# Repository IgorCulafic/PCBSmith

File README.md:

# PCBSmith

PCBSmith is an open-source tool for designing printed circuit boards. The long-term goal is to describe a circuit in plain language and get a checked schematic, board layout and manufacturing files. Today it combines a schematic editor prototype with KiCad-based workflows for automatic routing, design review and laser-fabricated boards.

It is under active development. The current tools support supervised engineering work: component choices, design decisions and physical testing still need a person.

[Board gallery](docs/showcase/README.md) · [Concept to board](docs/showcase/development-process.md) · [Get started](#get-started) · [Design workflow](docs/production-usage.md) · [Development](docs/development.md)

## Boards made with PCBSmith

These are retained images from actual design projects. Captions distinguish CAD results, work in progress and physical fabrication.

<table>
<tr>
<td width="50%" align="center">
<br>
<strong>Thermometer</strong><br>
63 components, 53 routed nets and a custom outline. Accepted CAD proof; the render uses some proxy models.
</td>
<td width="50%" align="center">
<br>
<strong>Eight-channel protocol analyzer</strong><br>
A more complex controller and input-interface study. Placement prototype; routing and review remain open.
</td>
</tr>
<tr>
<td width="50%" align="center">
<br>
<strong>Pear Worm</strong><br>
LED rings following a pear outline, with custom silkscreen. Historical design prototype.
</td>
<td width="50%" align="center">
<br>
<strong>Lucky Clover</strong><br>
A compact LED board with a four-lobed outline. Historical design prototype.
</td>
</tr>
<tr>
<td width="50%" align="center">
<br>
<strong>DuoFilter</strong><br>
Two-sided RC filter: automatic routing, a resistor revision and a checked CAD handover.
</td>
<td width="50%" align="center">
<br>
<strong>TraceLimits — recent laser test</strong><br>
0.15–1.00 mm traces, a six-net corner test and two isolation widths. CAD handover complete; process measurements pending.
</td>
</tr>
</table>

The [full gallery](docs/showcase/README.md) includes routing views, laser-artwork comparisons and a two-sided plated-hole test coupon.

### From CAD to copper

<p align="center">

</p>

An early single-sided laser test, photographed by the builder. The builder reported that the process worked and requested wider isolation channels for the next tests. This is a physical fabrication result; the newer trace-width and plating coupons are still awaiting measurements.

## What it can do today

- **Plan and edit circuits:** a schematic editor prototype, structured project data, component catalogs and CLI tools.
- **Work with KiCad:** native schematics and PCB files, component and footprint checks, electrical/design-rule checks, and 2D/3D review images.
- **Route boards automatically:** pinned Freerouting is the default for ordinary board jobs, with placement review and bounded retries.
- **Revise an existing design:** local board edits and reviewed component substitutions, including supported SMD replacements in the same footprint.
- **Prepare a handover:** editable vector floorplans, an interactive HTML BOM, Gerber/drill exports and recorded checks tied to the delivered board.
- **Prepare laser artwork:** single- and two-sided isolation SVG/PNG, pad-only coating-removal masks, and comparisons between retained background copper and locally cleared areas.

The main fabrication scope is single- and two-sided boards. Laser CAM currently supports documented straight-track/simple-pad geometry; unsupported cases are reported. See [current scope and limits](docs/current-state.md) for the details. A clean CAD check does not establish component fit, circuit operation or a qualified fabrication process.

## From concept to board

A finished render is one step in the process. Here is the same **TraceLimits**
board moving from a dimensioned concept to real copper geometry and laser artwork:

<table>
<tr>
<td width="33%" align="center"><br><strong>1. Concept and placement intent</strong><br>Board dimensions, probe positions and routing corridors.</td>
<td width="33%" align="center"><br><strong>2. Routed and checked PCB</strong><br>16 nets, 46 segments, front copper only.</td>
<td width="33%" align="center"><br><strong>3. Fabrication artwork</strong><br>Compare channel widths and background-copper removal.</td>
</tr>
</table>

The [illustrated development walkthrough](docs/showcase/development-process.md)
also shows the **schematic, 3D inspection, pad-only coating mask and interactive
BOM**, then explains the physical measurements still to come.
[Download the working BOM example](docs/showcase/assets/tracelimits-ibom.html?raw=1)
to open locally in a browser.

## Get started

The maintained development setup is **Python 3.12.12**, **uv 0.11.23** and **KiCad 10** with its symbol and footprint libraries. See [development setup](docs/development.md) for native-tool paths, optional dependencies and verification.

```powershell
git clone https://github.com/IgorCulafic/PCBSmith.git
cd PCBSmith
uv sync --frozen --all-extras --python 3.12.12
uv run --frozen --all-extras pcbsmith-gui
```

`pcbsmith-gui` opens the schematic editor prototype. Native board generation, review, routing and delivery use the separate [production CLI workflow](docs/production-usage.md).

To see CLI commands or run the standard developer checks:

```powershell
uv run --frozen --all-extras pcbsmith --help
uv run --frozen --all-extras python -B tools/verify.py --output .pcbsmith/verification/first-run
```

Choose a new verification output directory for each run. The standard checks cover the dependency lock, lint, types, architecture, workflow entry points and ordinary tests. The optional deep profile also requires live KiCad/ngspice tools.

## Documentation and contributing

- [Production usage](docs/production-usage.md): supported board creation, edits, routing and handover.
- [Development](docs/development.md) and [contributing](CONTRIBUTING.md): setup, verification and contribution boundaries.
- [Current state](docs/current-state.md) and [implementation records](docs/implementation/README.md): present scope and engineering detail.
- [Project history](docs/cli-foundations.md): the original headless Phase 0 CLI and architectural foundations.
- [Latest public software update](docs/github-update-2026-10-02.md): what was published and how it was checked.

## License

PCBSmith is licensed under [AGPL-3.0-or-later](LICENSE). Bundled KiCad library assets retain their own terms; see [third-party notices](THIRD_PARTY_NOTICES.md).

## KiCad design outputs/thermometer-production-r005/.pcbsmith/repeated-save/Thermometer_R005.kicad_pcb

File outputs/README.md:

Generated review bundles, fabrication packages, reports, and visual previews go here.

This directory is ignored by git except for this README.

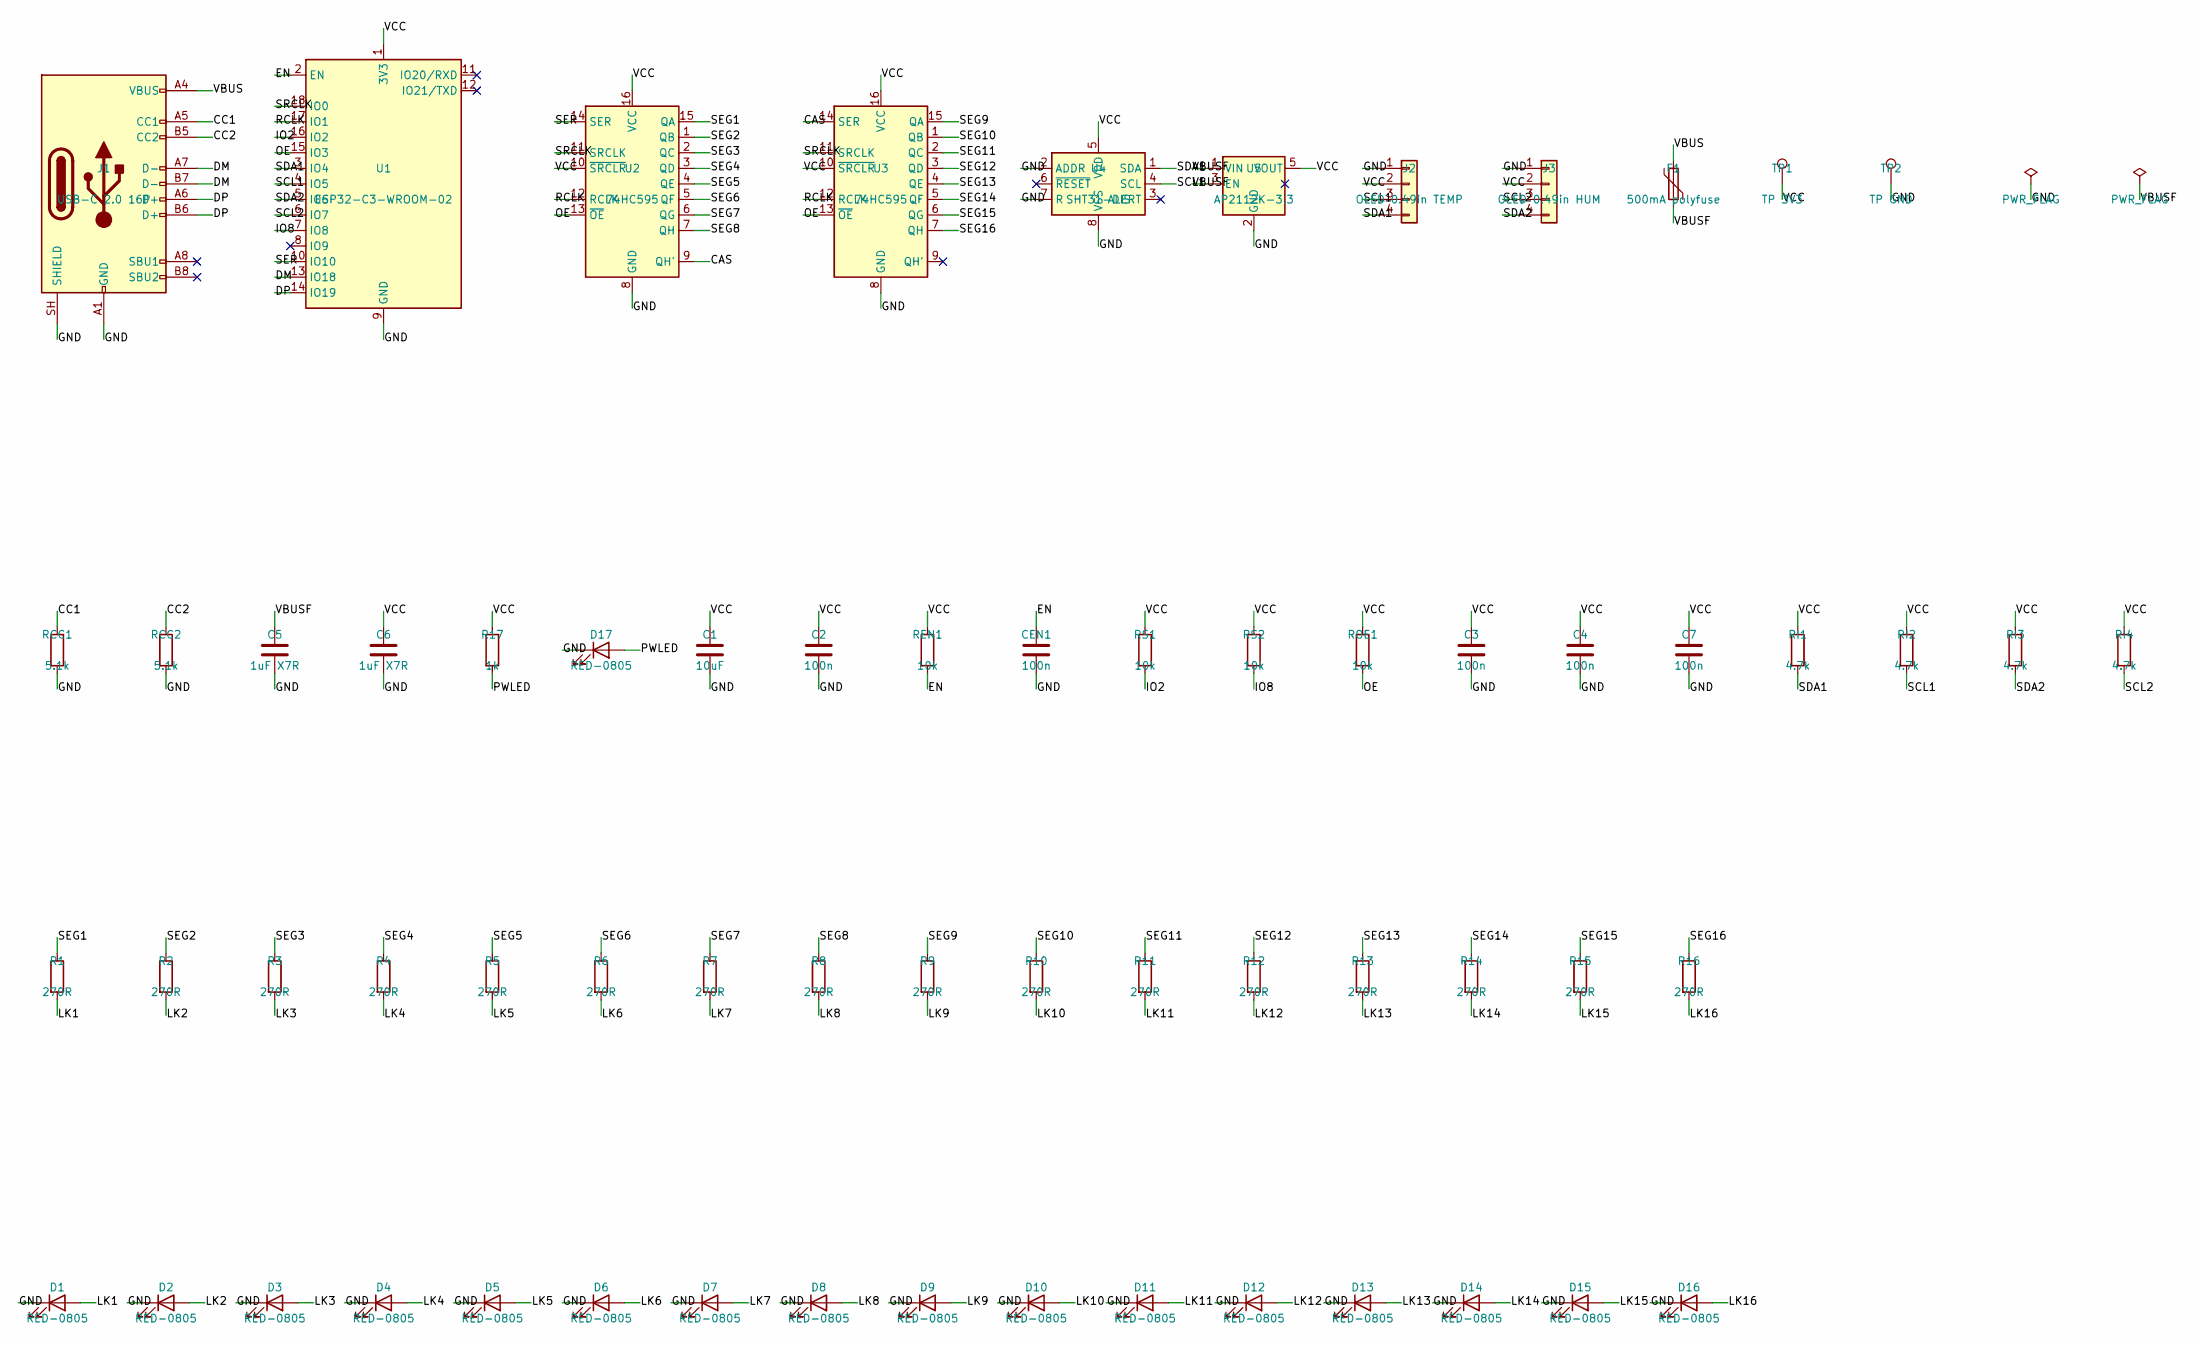
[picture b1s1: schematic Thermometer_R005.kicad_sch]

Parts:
C1: 10uF; C_0805_2012Metric
C2, C3, C4, C7: 100n; C_0603_1608Metric
C5, C6: 1uF X7R; C_0805_2012Metric
CEN1: 100n; C_0603_1608Metric
D1, D2, D3, D4, D5, D6, D7, D8, D9, D10, D11, D12, D13, D14, D15, D16, D17: RED-0805; LED_0805_2012Metric
F1: 500mA polyfuse; Fuse_1206_3216Metric
J1: USB-C 2.0 16P; USB_C_Receptacle_GCT_USB4105-xx-A_16P_TopMnt_Horizontal
J2: OLED 0.49in TEMP; PinHeader_1x04_P2.54mm_Vertical
J3: OLED 0.49in HUM; PinHeader_1x04_P2.54mm_Vertical
R1, R2, R3, R4, R5, R6, R7, R8, R9, R10, R11, R12, R13, R14, R15, R16: 270R; R_0603_1608Metric
R17: 1k; R_0603_1608Metric
RCC1, RCC2: 5.1k; R_0603_1608Metric
REN1: 10k; R_0603_1608Metric
RI1, RI2, RI3, RI4: 4.7k; R_0603_1608Metric
ROE1: 10k; R_0603_1608Metric
RS1, RS2: 10k; R_0603_1608Metric
TP1: TP 3V3; TestPoint_THTPad_D2.0mm_Drill1.0mm
TP2: TP GND; TestPoint_THTPad_D2.0mm_Drill1.0mm
U1: ESP32-C3-WROOM-02
U2, U3: 74HC595; TSSOP-16_4.4x5mm_P0.65mm
U4: SHT31-DIS; Sensirion_DFN-8-1EP_2.5x2.5mm_P0.5mm_EP1.1x1.7mm
U5: AP2112K-3.3; SOT-23-5

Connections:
/CAS: U2.9 (QH'), U3.14 (SER)
/CC1: J1.A5 (CC1), RCC1.1
/CC2: J1.B5 (CC2), RCC2.1
/DM: J1.A7 (D-), J1.B7 (D-), U1.13 (IO18)
/DP: J1.A6 (D+), J1.B6 (D+), U1.14 (IO19)
/EN: CEN1.1, REN1.2, U1.2 (EN)
/GND: C1.2, C2.2, C3.2, C4.2, C5.2, C6.2, C7.2, CEN1.2, D1.1 (K), D2.1 (K), D3.1 (K), D4.1 (K), D5.1 (K), D6.1 (K), D7.1 (K), D8.1 (K), D9.1 (K), D10.1 (K), D11.1 (K), D12.1 (K), D13.1 (K), D14.1 (K), D15.1 (K), D16.1 (K), D17.1 (K), J1.A1 (GND), J1.A12 (GND), J1.B1 (GND), J1.B12 (GND), J1.SH (SHIELD), J2.1, J3.1, RCC1.2, RCC2.2, TP2.1, U1.9 (GND), U1.19 (GND), U2.8 (GND), U3.8 (GND), U4.2 (ADDR), U4.7 (R), U4.8 (VSS), U4.9 (VSS), U5.2 (GND)
/IO2: RS1.2, U1.16 (IO2)
/IO8: RS2.2, U1.7 (IO8)
/LK1: D1.2 (A), R1.2
/LK2: D2.2 (A), R2.2
/LK3: D3.2 (A), R3.2
/LK4: D4.2 (A), R4.2
/LK5: D5.2 (A), R5.2
/LK6: D6.2 (A), R6.2
/LK7: D7.2 (A), R7.2
/LK8: D8.2 (A), R8.2
/LK9: D9.2 (A), R9.2
/LK10: D10.2 (A), R10.2
/LK11: D11.2 (A), R11.2
/LK12: D12.2 (A), R12.2
/LK13: D13.2 (A), R13.2
/LK14: D14.2 (A), R14.2
/LK15: D15.2 (A), R15.2
/LK16: D16.2 (A), R16.2
/OE: ROE1.2, U1.15 (IO3), U2.13 (~OE), U3.13 (~OE)
/PWLED: D17.2 (A), R17.2
/RCLK: U1.17 (IO1), U2.12 (RCLK), U3.12 (RCLK)
/SCL1: J2.3, RI2.2, U1.4 (IO5), U4.4 (SCL)
/SCL2: J3.3, RI4.2, U1.6 (IO7)
/SDA1: J2.4, RI1.2, U1.3 (IO4), U4.1 (SDA)
/SDA2: J3.4, RI3.2, U1.5 (IO6)
/SEG1: R1.1, U2.15 (QA)
/SEG2: R2.1, U2.1 (QB)
/SEG3: R3.1, U2.2 (QC)
/SEG4: R4.1, U2.3 (QD)
/SEG5: R5.1, U2.4 (QE)
/SEG6: R6.1, U2.5 (QF)
/SEG7: R7.1, U2.6 (QG)
/SEG8: R8.1, U2.7 (QH)
/SEG9: R9.1, U3.15 (QA)
/SEG10: R10.1, U3.1 (QB)
/SEG11: R11.1, U3.2 (QC)
/SEG12: R12.1, U3.3 (QD)
/SEG13: R13.1, U3.4 (QE)
/SEG14: R14.1, U3.5 (QF)
/SEG15: R15.1, U3.6 (QG)
/SEG16: R16.1, U3.7 (QH)
/SER: U1.10 (IO10), U2.14 (SER)
/SRCLK: U1.18 (IO0), U2.11 (SRCLK), U3.11 (SRCLK)
/VBUS: F1.1, J1.A4 (VBUS), J1.A9 (VBUS), J1.B4 (VBUS), J1.B9 (VBUS)
/VBUSF: C5.1, F1.2, U5.1 (VIN), U5.3 (EN)
/VCC: C1.1, C2.1, C3.1, C4.1, C6.1, C7.1, J2.2, J3.2, R17.1, REN1.1, RI1.1, RI2.1, RI3.1, RI4.1, ROE1.1, RS1.1, RS2.1, TP1.1, U1.1 (3V3), U2.10 (~SRCLR), U2.16 (VCC), U3.10 (~SRCLR), U3.16 (VCC), U4.5 (VDD), U5.5 (VOUT)

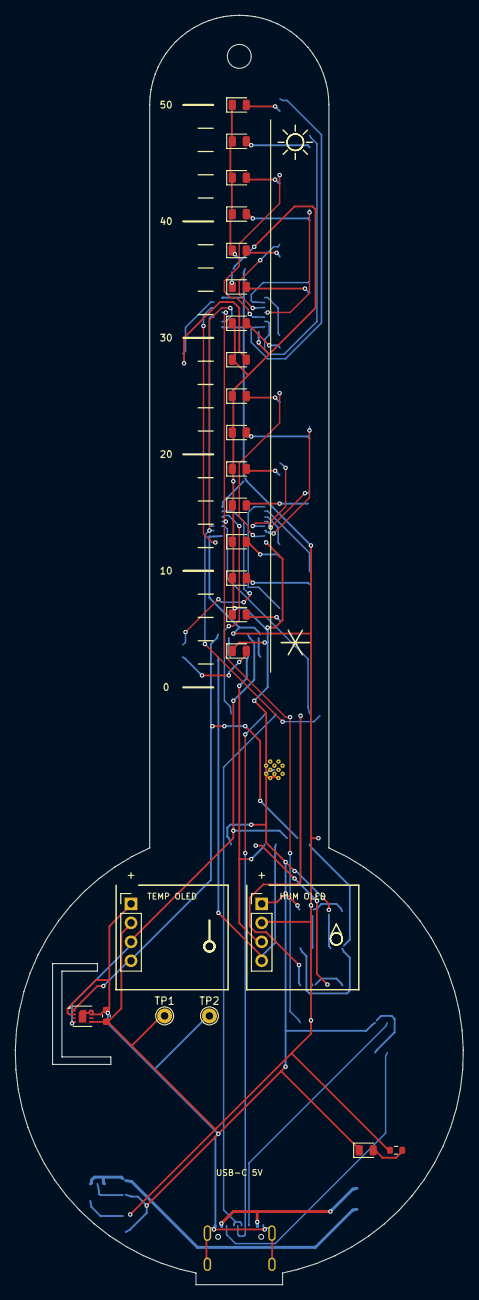
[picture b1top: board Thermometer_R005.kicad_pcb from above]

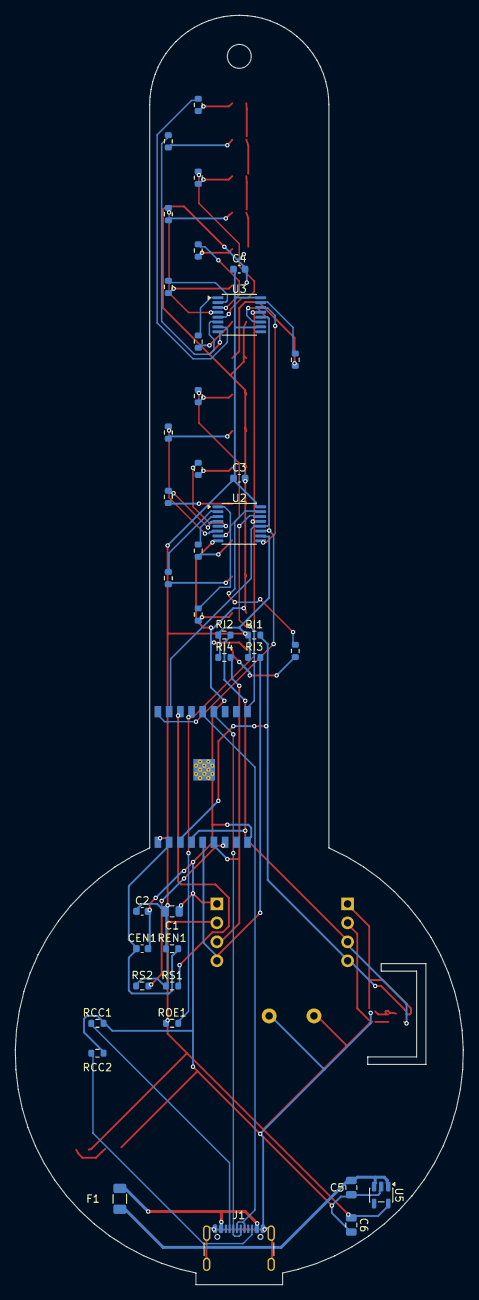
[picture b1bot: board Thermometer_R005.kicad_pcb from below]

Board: 2 copper layers, 60.0 x 170.0 mm, 64 parts (39 on the bottom side), 53 nets.

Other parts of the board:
H1: M3; MountingHole_3.2mm_M3

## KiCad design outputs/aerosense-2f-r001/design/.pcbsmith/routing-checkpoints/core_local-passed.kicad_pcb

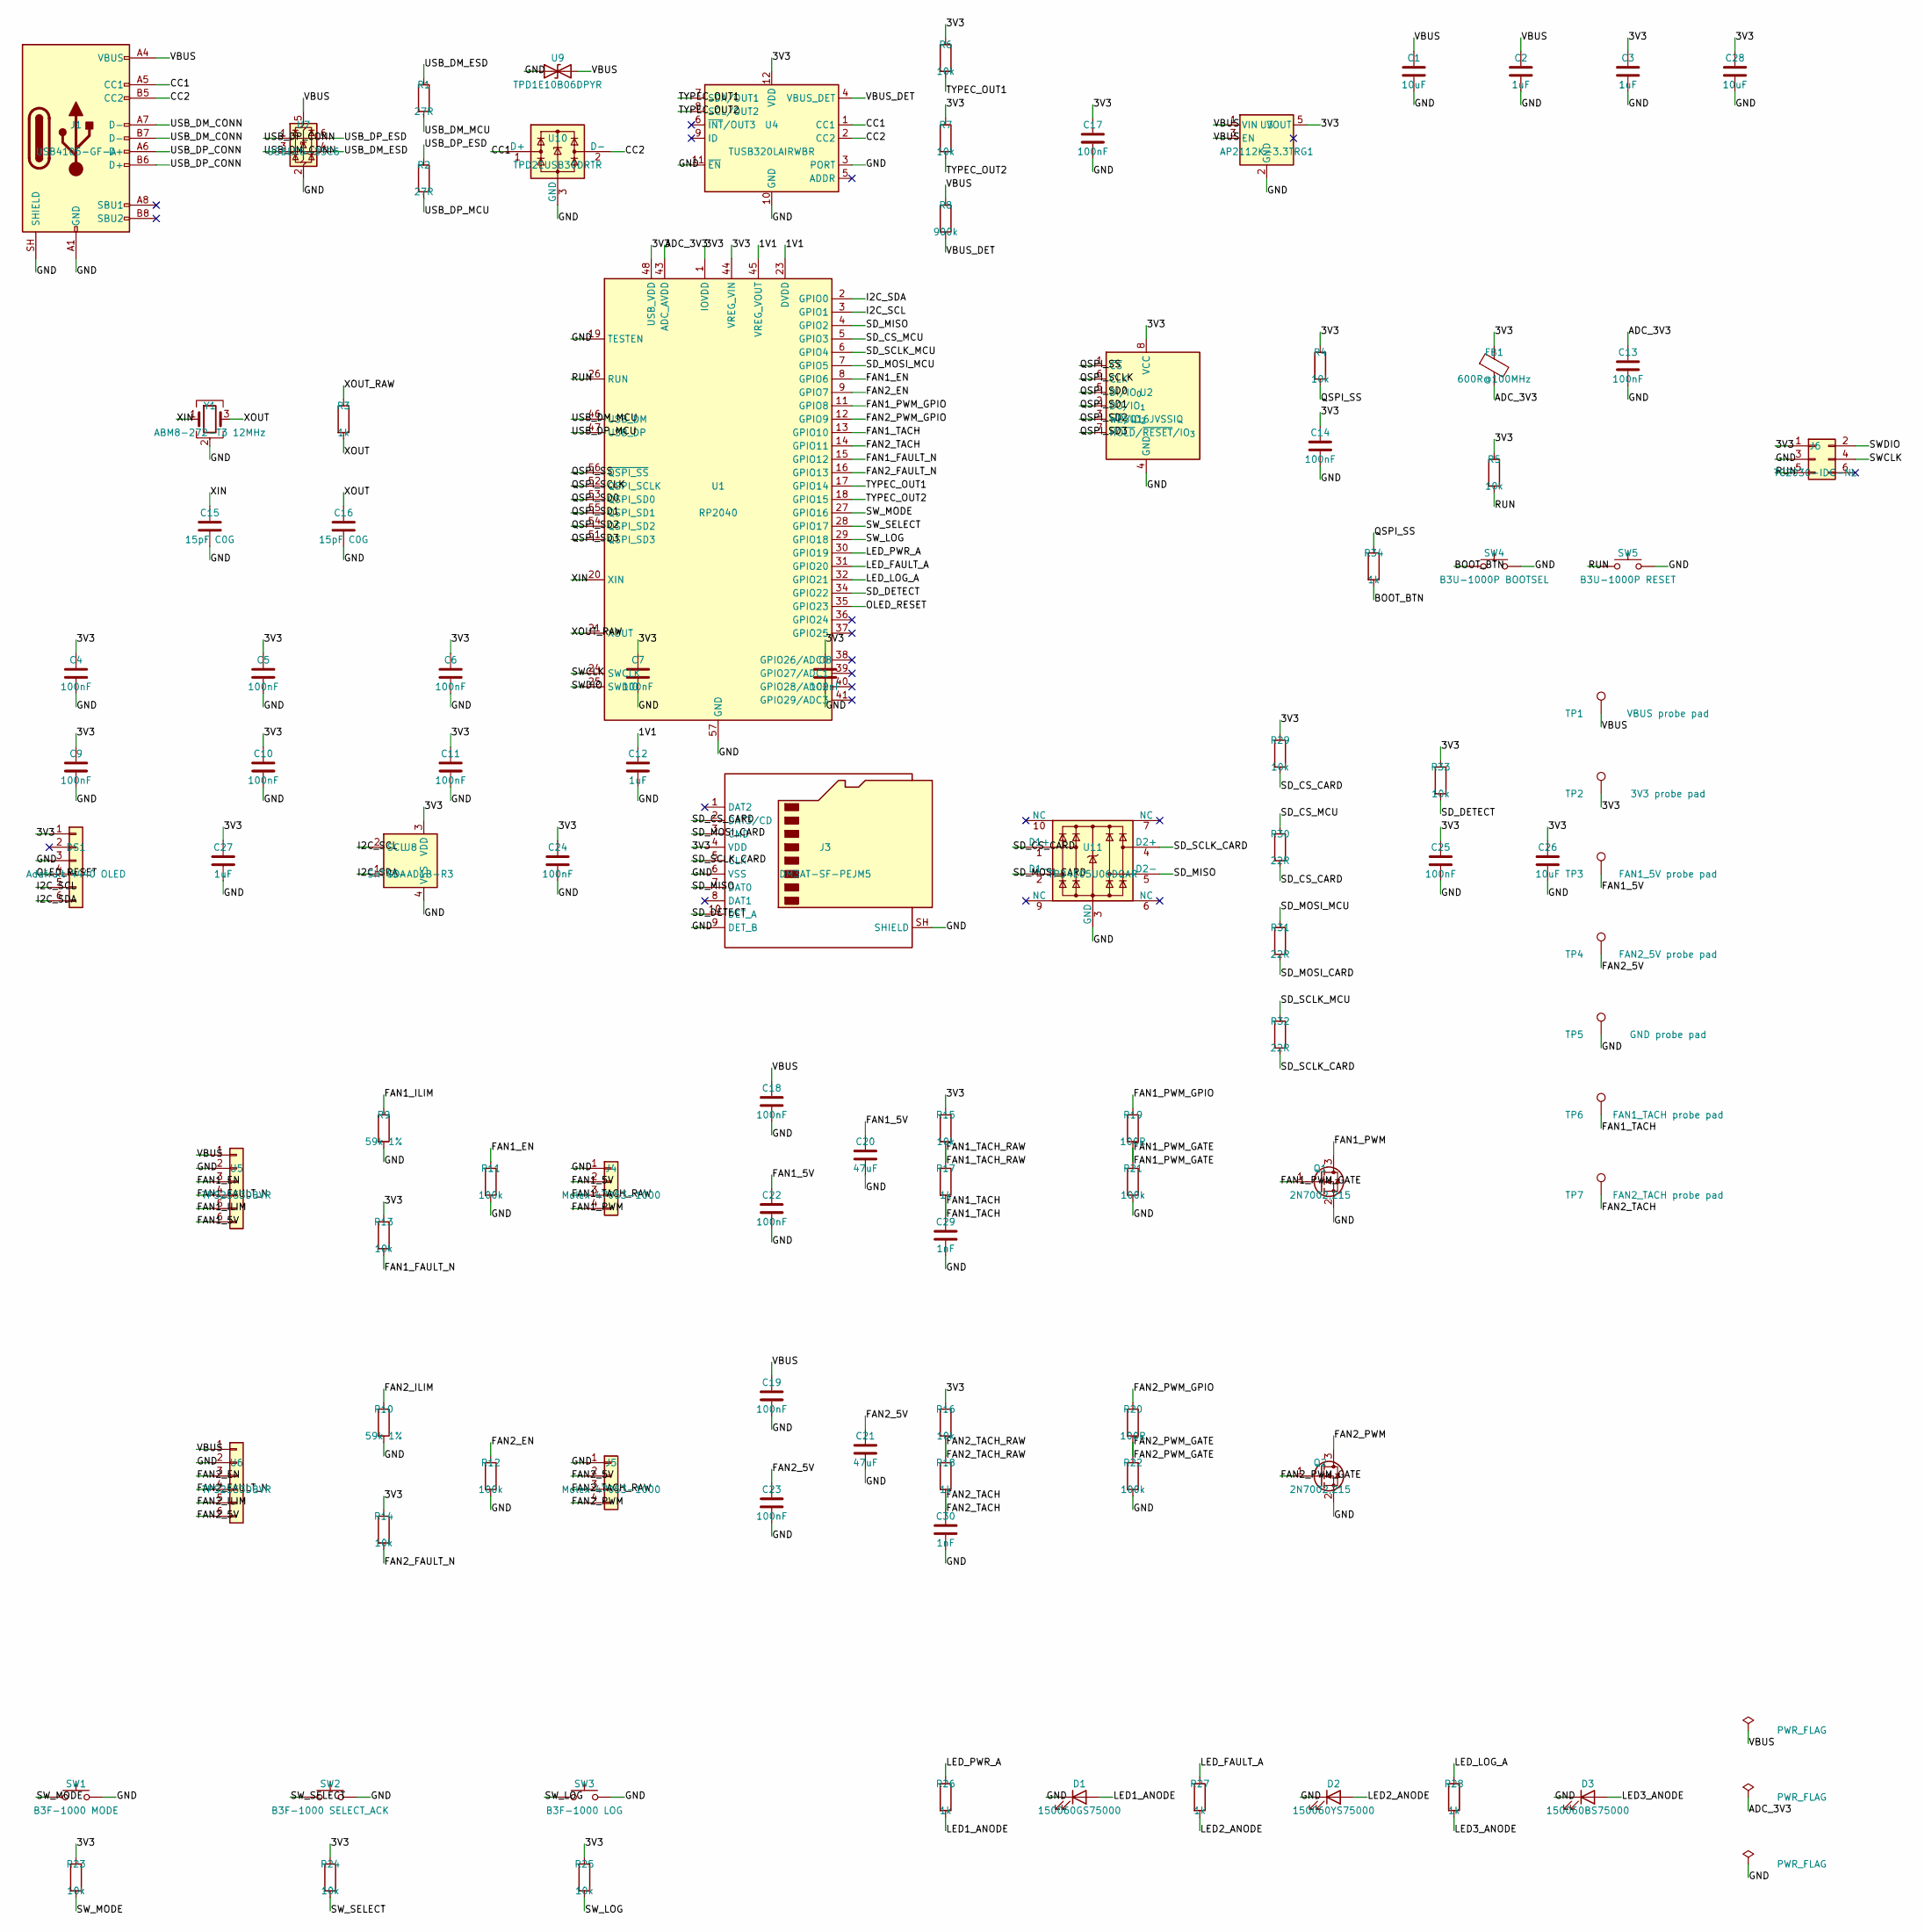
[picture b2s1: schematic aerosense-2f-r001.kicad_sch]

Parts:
C1, C26, C28: 10uF; C_0805_2012Metric
C2, C3: 1uF; C_0805_2012Metric
C4, C5, C6, C7, C8, C9, C10, C11, C13, C14, C17, C18, C19, C22, C23, C24, C25: 100nF; C_0603_1608Metric
C12, C27: 1uF; C_0603_1608Metric
C15, C16: 15pF C0G; C_0603_1608Metric
C20, C21: 47uF; C_0805_2012Metric
C29, C30: 1nF; C_0603_1608Metric
D1: 150060GS75000; LED_0603_1608Metric
D2: 150060YS75000; LED_0603_1608Metric
D3: 150060BS75000; LED_0603_1608Metric
DS1: Adafruit 4440 OLED; Adafruit_4440_OLED_Module
FB1: 600R@100MHz; L_0603_1608Metric
J1: USB4105-GF-A; USB_C_Receptacle_GCT_USB4105-xx-A_16P_TopMnt_Horizontal
J3: DM3AT-SF-PEJM5; microSD_HC_Hirose_DM3AT-SF-PEJM5
J4, J5: Molex 47053-1000; FanPinHeader_1x04_P2.54mm_Vertical
J6: TC2030-IDC-NL; Tag-Connect_TC2030-IDC-NL_2x03_P1.27mm_Vertical
Q1, Q2: 2N7002,215; SOT-23
R1, R2: 27R; R_0603_1608Metric
R3, R17, R18, R26, R27, R28, R34: 1k; R_0603_1608Metric
R4, R5, R6, R7, R13, R14, R15, R16, R23, R24, R25, R29, R33: 10k; R_0603_1608Metric
R8: 900k; R_0603_1608Metric
R9, R10: 59k 1%; R_0603_1608Metric
R11, R12, R21, R22: 100k; R_0603_1608Metric
R19, R20: 100R; R_0603_1608Metric
R30, R31, R32: 22R; R_0603_1608Metric
SW1: B3F-1000 MODE; SW_PUSH_6mm_H4.3mm
SW2: B3F-1000 SELECT_ACK; SW_PUSH_6mm_H4.3mm
SW3: B3F-1000 LOG; SW_PUSH_6mm_H4.3mm
SW4: B3U-1000P BOOTSEL; SW_SPST_B3U-1000P
SW5: B3U-1000P RESET; SW_SPST_B3U-1000P
TP1: VBUS probe pad; TestPoint_Pad_D1.0mm
TP2: 3V3 probe pad; TestPoint_Pad_D1.0mm
TP3: FAN1_5V probe pad; TestPoint_Pad_D1.0mm
TP4: FAN2_5V probe pad; TestPoint_Pad_D1.0mm
TP5: GND probe pad; TestPoint_Pad_D1.0mm
TP6: FAN1_TACH probe pad; TestPoint_Pad_D1.0mm
TP7: FAN2_TACH probe pad; TestPoint_Pad_D1.0mm
U1: RP2040; QFN-56-1EP_7x7mm_P0.4mm_EP3.2x3.2mm_ThermalVias
U2: W25Q16JVSSIQ; SOIC-8_3.9x4.9mm_P1.27mm
U3: AP2112K-3.3TRG1; SOT-23-5
U4: TUSB320LAIRWBR; TUSB320_X2QFN12
U5, U6: TPS2553DBVR; SOT-23-6
U7: USBLC6-2SC6; SOT-23-6
U8: SHT45-AD1B-R3; Sensirion_SHT45_NoCentralPad
U9: TPD1E10B06DPYR; TPD1E10B06_DPY2
U10: TPD2EUSB30DRTR; Texas_DRT-3
U11: TPD4E05U06DQAR; USON-10_2.5x1.0mm_P0.5mm
Y1: ABM8-272-T3 12MHz; Crystal_SMD_Abracon_ABM8G-4Pin_3.2x2.5mm

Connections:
/1V1: C12.1, U1.23 (DVDD), U1.45 (VREG_VOUT), U1.50 (DVDD)
/3V3: C3.1, C4.1, C5.1, C6.1, C7.1, C8.1, C9.1, C10.1, C11.1, C14.1, C17.1, C24.1, C25.1, C26.1, C27.1, C28.1, DS1.1, FB1.1, J3.4 (VDD), J6.1, R4.1, R5.1, R6.1, R7.1, R13.1, R14.1, R15.1, R16.1, R23.1, R24.1, R25.1, R29.1, R33.1, TP2.1, U1.1 (IOVDD), U1.10 (IOVDD), U1.22 (IOVDD), U1.33 (IOVDD), U1.42 (IOVDD), U1.44 (VREG_VIN), U1.48 (USB_VDD), U1.49 (IOVDD), U2.8 (VCC), U3.5 (VOUT), U4.12 (VDD), U8.3 (VDD)
/ADC_3V3: C13.1, FB1.2, U1.43 (ADC_AVDD)
/BOOT_BTN: R34.2, SW4.1
/CC1: J1.A5 (CC1), U4.1 (CC1), U10.1 (D+)
/CC2: J1.B5 (CC2), U4.2 (CC2), U10.2 (D-)
/FAN1_5V: C20.1, C22.1, J4.2, TP3.1, U5.6
/FAN1_EN: R11.1, U1.8 (GPIO6), U5.3
/FAN1_FAULT_N: R13.2, U1.15 (GPIO12), U5.4
/FAN1_ILIM: R9.1, U5.5
/FAN1_PWM: J4.4, Q1.3 (D)
/FAN1_PWM_GATE: Q1.1 (G), R19.2, R21.1
/FAN1_PWM_GPIO: R19.1, U1.11 (GPIO8)
/FAN1_TACH: C29.1, R17.2, TP6.1, U1.13 (GPIO10)
/FAN1_TACH_RAW: J4.3, R15.2, R17.1
/FAN2_5V: C21.1, C23.1, J5.2, TP4.1, U6.6
/FAN2_EN: R12.1, U1.9 (GPIO7), U6.3
/FAN2_FAULT_N: R14.2, U1.16 (GPIO13), U6.4
/FAN2_ILIM: R10.1, U6.5
/FAN2_PWM: J5.4, Q2.3 (D)
/FAN2_PWM_GATE: Q2.1 (G), R20.2, R22.1
/FAN2_PWM_GPIO: R20.1, U1.12 (GPIO9)
/FAN2_TACH: C30.1, R18.2, TP7.1, U1.14 (GPIO11)
/FAN2_TACH_RAW: J5.3, R16.2, R18.1
/GND: C1.2, C2.2, C3.2, C4.2, C5.2, C6.2, C7.2, C8.2, C9.2, C10.2, C11.2, C12.2, C13.2, C14.2, C15.2, C16.2, C17.2, C18.2, C19.2, C20.2, C21.2, C22.2, C23.2, C24.2, C25.2, C26.2, C27.2, C28.2, C29.2, C30.2, D1.1 (K), D2.1 (K), D3.1 (K), DS1.3, J1.A1 (GND), J1.A12 (GND), J1.B1 (GND), J1.B12 (GND), J1.SH (SHIELD), J3.6 (VSS), J3.9 (DET_B), J3.SH (SHIELD), J4.1, J5.1, J6.3, Q1.2 (S), Q2.2 (S), R9.2, R10.2, R11.2, R12.2, R21.2, R22.2, SW1.2, SW2.2, SW3.2, SW4.2, SW5.2, TP5.1, U1.19 (TESTEN), U1.57 (GND), U2.4 (GND), U3.2 (GND), U4.3 (PORT), U4.10 (GND), U4.11 (~EN), U5.2, U6.2, U7.2 (GND), U8.4 (VSS), U9.1 (A1), U10.3 (GND), U11.3 (GND), U11.8 (GND), Y1.2 (G), Y1.4 (G)
/I2C_SCL: DS1.5, U1.3 (GPIO1), U8.2 (SCL)
/I2C_SDA: DS1.6, U1.2 (GPIO0), U8.1 (SDA)
/LED1_ANODE: D1.2 (A), R26.2
/LED2_ANODE: D2.2 (A), R27.2
/LED3_ANODE: D3.2 (A), R28.2
/LED_FAULT_A: R27.1, U1.31 (GPIO20)
/LED_LOG_A: R28.1, U1.32 (GPIO21)
/LED_PWR_A: R26.1, U1.30 (GPIO19)
/OLED_RESET: DS1.4, U1.35 (GPIO23)
/QSPI_SCLK: U1.52 (QSPI_SCLK), U2.6 (CLK)
/QSPI_SD0: U1.53 (QSPI_SD0), U2.5 (DI/IO_{0})
/QSPI_SD1: U1.55 (QSPI_SD1), U2.2 (DO/IO_{1})
/QSPI_SD2: U1.54 (QSPI_SD2), U2.3 (~WP/IO_{2})
/QSPI_SD3: U1.51 (QSPI_SD3), U2.7 (~HOLD/~RESET/IO_{3})
/QSPI_SS: R4.2, R34.1, U1.56 (~QSPI_SS), U2.1 (~CS)
/RUN: J6.5, R5.2, SW5.1, U1.26 (RUN)
/SD_CS_CARD: J3.2 (DAT3/CD), R29.2, R30.2, U11.1 (D1+)
/SD_CS_MCU: R30.1, U1.5 (GPIO3)
/SD_DETECT: J3.10 (DET_A), R33.2, U1.34 (GPIO22)
/SD_MISO: J3.7 (DAT0), U1.4 (GPIO2), U11.5 (D2-)
/SD_MOSI_CARD: J3.3 (CMD), R31.2, U11.2 (D1-)
/SD_MOSI_MCU: R31.1, U1.7 (GPIO5)
/SD_SCLK_CARD: J3.5 (CLK), R32.2, U11.4 (D2+)
/SD_SCLK_MCU: R32.1, U1.6 (GPIO4)
/SWCLK: J6.4, U1.24 (SWCLK)
/SWDIO: J6.2, U1.25 (SWDIO)
/SW_LOG: R25.2, SW3.1, U1.29 (GPIO18)
/SW_MODE: R23.2, SW1.1, U1.27 (GPIO16)
/SW_SELECT: R24.2, SW2.1, U1.28 (GPIO17)
/TYPEC_OUT1: R6.2, U1.17 (GPIO14), U4.7 (SDA/OUT1)
/TYPEC_OUT2: R7.2, U1.18 (GPIO15), U4.8 (SCL/OUT2)
/USB_DM_CONN: J1.A7 (D-), J1.B7 (D-), U7.3 (I/O2)
/USB_DM_ESD: R1.1, U7.4 (I/O2)
/USB_DM_MCU: R1.2, U1.46 (USB_DM)
/USB_DP_CONN: J1.A6 (D+), J1.B6 (D+), U7.1 (I/O1)
/USB_DP_ESD: R2.1, U7.6 (I/O1)
/USB_DP_MCU: R2.2, U1.47 (USB_DP)
/VBUS: C1.1, C2.1, C18.1, C19.1, J1.A4 (VBUS), J1.A9 (VBUS), J1.B4 (VBUS), J1.B9 (VBUS), R8.1, TP1.1, U3.1 (VIN), U3.3 (EN), U5.1, U6.1, U7.5 (VBUS), U9.2 (A2)
/VBUS_DET: R8.2, U4.4 (VBUS_DET)
/XIN: C15.1, U1.20 (XIN), Y1.1
/XOUT: C16.1, R3.2, Y1.3
/XOUT_RAW: R3.1, U1.21 (XOUT)

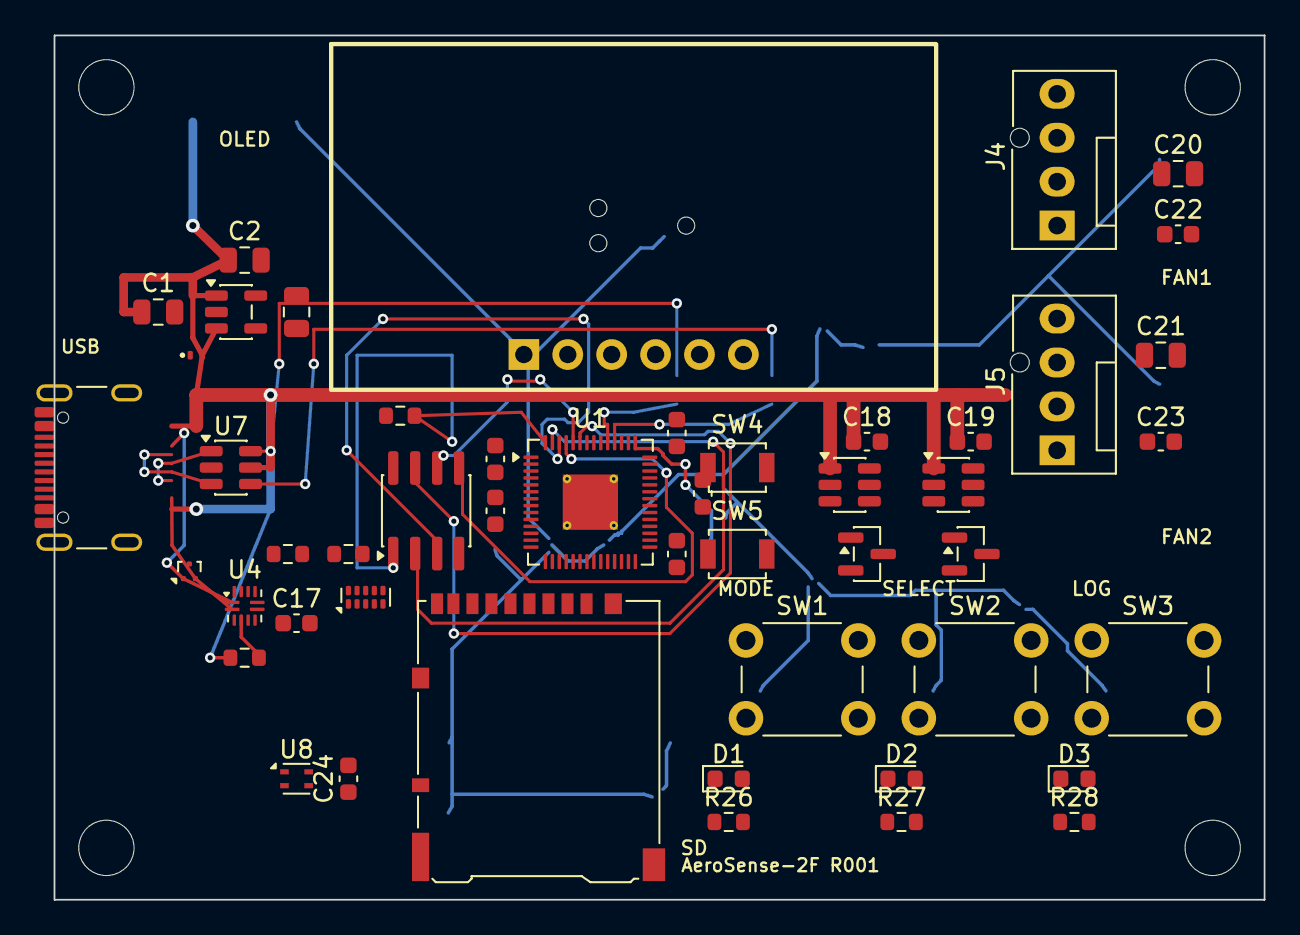
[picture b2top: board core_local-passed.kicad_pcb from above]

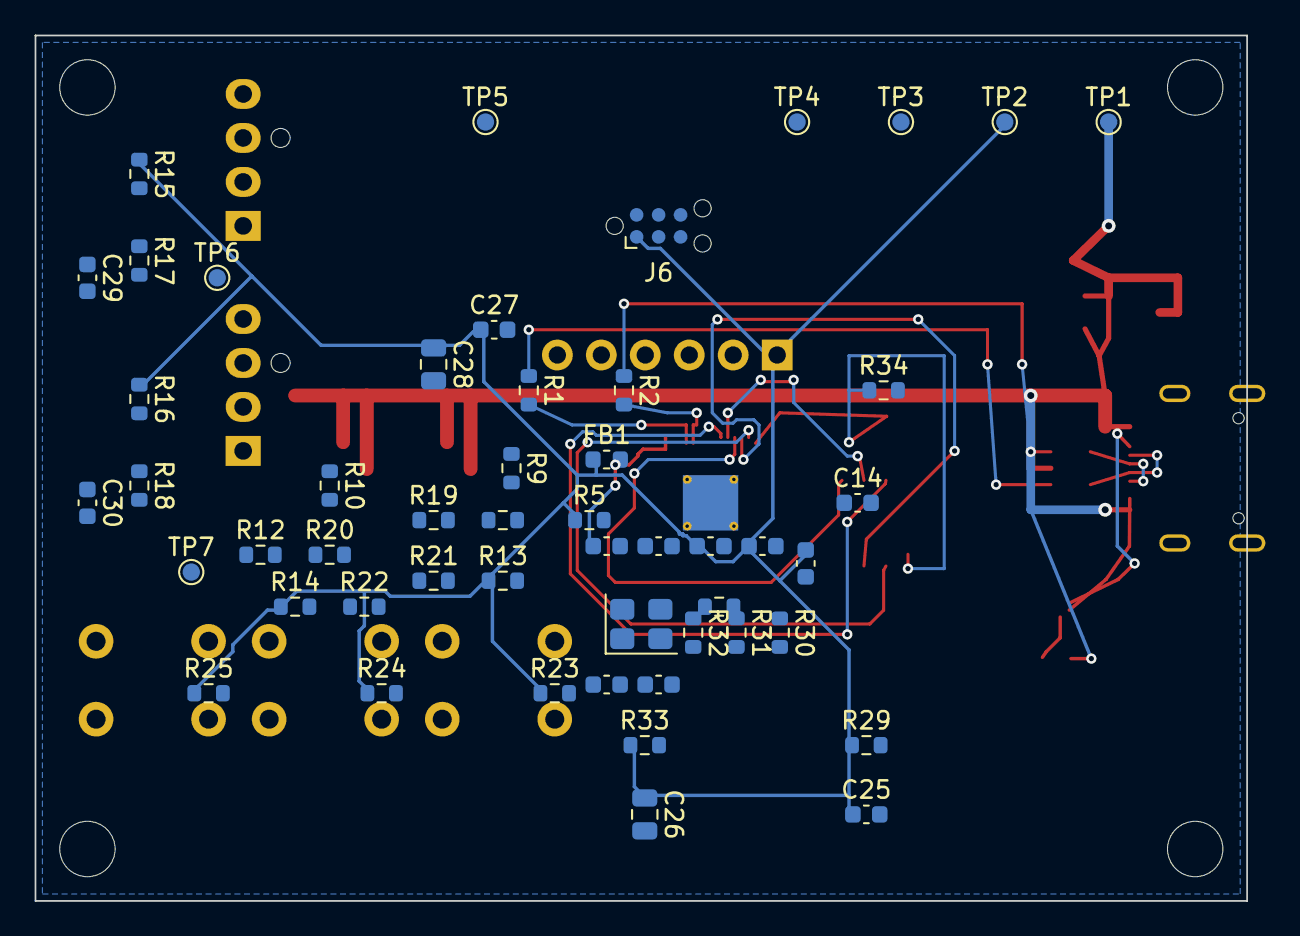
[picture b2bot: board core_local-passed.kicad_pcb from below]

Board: 2 copper layers, 70.0 x 50.0 mm, 104 parts (51 on the bottom side), 67 nets.

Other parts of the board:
H1, H2, H3, H4: M3 NPTH; MountingHole_3.2mm_M3

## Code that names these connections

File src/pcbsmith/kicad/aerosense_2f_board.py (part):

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                "/FAN2_FAULT_N",
                "/FAN1_ILIM",
                "/FAN2_ILIM",
                "/FAN1_PWM_GPIO",
                "/FAN2_PWM_GPIO",
                "/FAN1_PWM_GATE",
                "/FAN2_PWM_GATE",
                "/FAN1_PWM",
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
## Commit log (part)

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2026-05-10 test: update gui placement expectations
2026-05-10 style: format gui placement tests
2026-05-10 feat: persist horizontal symbol mirror
2026-05-10 fix: apply light gui chrome
2026-05-10 feat: polish editor palette and shortcuts
2026-05-10 feat: center startup view and grid units
2026-05-10 feat: add schematic command spine
2026-05-10 feat: snap wires to schematic anchors
2026-05-10 feat: pivot toward kicad backend
2026-05-10 feat: create kicad project skeletons
2026-05-10 feat: export pcbs projects to kicad handoff
2026-05-10 feat: verify kicad backend readiness
2026-05-10 feat: add kicad validation command
2026-05-10 feat: export schematic primitives to kicad
2026-05-10 fix: avoid dangling kicad labels
2026-05-10 fix: keep unconnected primitives out of kicad export
2026-05-10 feat: export native kicad symbols
2026-05-10 feat: export common kicad symbols
2026-05-10 fix: place kicad exports inside sheet
2026-05-10 docs: capture ai companion strategy
2026-05-10 feat: add led series kicad fixture
2026-05-10 fix: hide electrical power endpoint labels
2026-05-10 feat: add kicad command approval loop
2026-05-10 feat: add ai context package export
2026-05-10 chore: add workspace maintenance tools
2026-05-10 feat: add kicad preview export
2026-05-10 chore: commit uv lockfile
2026-05-10 feat: add kicad review bundle
2026-05-10 feat: add ai engineering briefs
2026-05-10 feat: add ai planner package contract
2026-05-10 feat: add ai plan contract validation
2026-05-10 feat: add ai plan approval preview
2026-05-10 feat: add deterministic ai demo planner
2026-05-10 feat: add kicad library index
2026-05-10 feat: add visible ai led demo flow
2026-05-10 fix: hide internal demo net labels
2026-05-10 feat: add kicad board preview handoff
2026-05-10 feat: add voltage divider ai demo
2026-05-10 feat: add rc filter ai demo
2026-05-10 fix: render symbol pin leads
2026-05-10 fix: hide generated interior net labels
2026-05-10 feat: add openai compatible planner adapter
2026-05-10 feat: add openai compatible review pipeline
2026-05-10 feat: add ai proposal preview bundles
2026-05-10 fix: center generated kicad schematics
2026-05-10 feat: add kicad catalog part resolution
2026-05-10 fix: center generated kicad boards
2026-05-10 docs: specify layer-aware board groundwork
2026-05-10 feat: add layer-aware board groundwork
2026-05-10 feat: add board ai commands
2026-05-11 feat: add branched circuit demo
2026-05-11 feat: export laser copper svg preview
2026-05-11 feat: export manufacturable routing artifacts
2026-05-11 fix: route ground away from demo components
2026-05-11 feat: add VIR LAB LED board generator
2026-05-11 feat: polish VIR LAB LED demo output
2026-05-11 feat: add reusable KiCad board builder
2026-05-11 feat: add schematic-backed LED example
2026-05-11 feat: add toggleable anode polarity marks
2026-05-11 feat: add component silkscreen markings
2026-05-11 fix: remove legacy footprint silk ticks
2026-05-11 feat: add schematic-backed rc filter demo
2026-05-11 feat: add schematic-backed 555 astable demo
2026-05-11 fix: polish generated 555 board placement
2026-05-11 feat: add board routing intelligence
2026-05-11 feat: add configurable routing style preference
2026-05-11 feat: add 555 pwm dimmer demo
2026-05-11 fix: polish pwm dimmer routing style
2026-05-11 feat: add native pwm schematic symbols
2026-05-11 feat: add board manufacturability checks
2026-05-12 feat: include manufacturability report in review bundles
2026-05-12 docs: add LED art roadmap
2026-05-12 feat: add R0 LED art planning report
2026-05-12 feat: add LED art topology comparison
2026-05-12 feat: generate dense LED art board variants
2026-05-12 feat: chain adjacent LED art strings
2026-05-12 feat: add switched LED art control mode
2026-05-12 refactor: move LED art board rules into service
2026-05-12 feat: add LED art design operation
2026-05-12 feat: add component knowledge index
2026-05-12 refactor: centralize board routing rules
2026-05-12 chore: finish design operation cleanup
2026-05-12 feat: expand component knowledge catalog
2026-05-12 feat: add component knowledge search
2026-05-12 feat: add intent-based component selection
2026-05-12 feat: expose component selection to AI packages
2026-05-12 feat: add circuit rule checks
2026-05-13 feat: add AI revision briefs
2026-05-13 docs: separate board artwork and outline roadmap
2026-05-13 feat: complete revision brief review loop
2026-05-13 feat: add R6 ATtiny LED controller demo
2026-05-13 fix: fan out vias from SMD pads
2026-05-13 fix: simplify ATtiny ground return routing
2026-05-14 fix: merge ATtiny ground branches onto one trunk
2026-05-14 feat: centralize board annotation conventions
2026-05-14 fix: clean ATtiny helper silkscreen labels
2026-05-14 feat: add selectable ATtiny ISP connector styles
2026-05-16 feat: add board feature intent guardrails
2026-05-16 feat: add silkscreen artwork preflight
2026-05-16 feat: add silkscreen artwork design operation
2026-05-16 feat: add silkscreen graphic primitives
2026-05-17 feat: add board outline geometry foundation
2026-05-17 chore: ignore R8 archive directory
2026-05-17 refactor: split service modules into architecture packages
2026-05-17 fix: add visible placeholders for board-only schematics
2026-05-17 feat: add composable circuit blocks
2026-05-17 feat: add R9 circuit template registry
2026-05-17 Add circuit intelligence foundation
2026-05-17 Add deterministic calculator foundation
2026-05-17 Add validation reporting layer
2026-05-17 Expand R13 component catalog
2026-05-17 Add local AI endpoint integration
2026-05-17 Handle noisy local model JSON responses
2026-05-17 Add local AI tool agent loop
2026-05-18 Add training data logging structure
2026-05-18 Demote flawed buck output in training data
2026-05-18 Add global KiCad board policy gate
2026-05-18 Add LM2596 buck converter generator
2026-05-18 Add reset handoff for simulation-first architecture
2026-05-18 feat: add circuit intelligence domain models
2026-05-18 feat: classify first circuit topology
2026-05-18 feat: add deterministic passive calculators
2026-05-18 feat: compose first validated circuit object
2026-05-18 feat: add ngspice simulation wrapper
2026-05-18 feat: generate schematic-first divider highpass led project
2026-05-18 feat: write first circuit review bundle
2026-05-18 feat: add circuit intelligence vertical slice cli
2026-05-18 style: wrap circuit slice review messages
2026-05-18 docs: add circuit intelligence roadmap and plan
2026-05-18 fix: capture ngspice measurements
2026-05-18 refactor: generalize ngspice batch evidence
2026-05-18 docs: specify kicad ngspice authority flow
2026-05-19 docs: add authority revision loop
2026-05-19 docs: plan kicad ngspice authority slice
2026-05-19 feat: add kicad cli runner
2026-05-19 feat: add authority report models
2026-05-19 fix: export authority circuit models
2026-05-19 feat: export divider slice to kicad
2026-05-19 fix: make kicad slice schematic loadable
2026-05-19 fix: align kicad slice schematic connectivity
2026-05-19 fix: preserve slice net separation
2026-05-19 feat: run kicad erc validation
2026-05-19 fix: harden kicad erc report parsing
2026-05-19 feat: run ngspice from kicad spice netlists
2026-05-19 fix: harden kicad spice ngspice netlist handling
2026-05-19 fix: run ngspice netlists from source directory
2026-05-19 fix: resolve existing ngspice netlist paths
2026-05-19 feat: add authority revision records
2026-05-19 fix: harden authority revision routing
2026-05-19 feat: write authority review bundles
2026-05-19 chore: sort circuit exports
2026-05-19 fix: harden review bundle status derivation
2026-05-19 feat: add authority circuit slice cli
2026-05-19 fix: clarify authority cli simulation evidence
2026-05-19 fix: make kicad authority smoke simulatable
2026-05-20 feat: add cache-backed component evidence selection
2026-05-20 feat: add evidence acquisition cache writer
2026-05-20 feat: add mocked Nexar evidence provider
2026-05-20 feat: add opt-in Nexar OAuth smoke
2026-05-20 feat: stage cached datasheets for extraction
2026-05-20 feat: add evidence extraction worker
